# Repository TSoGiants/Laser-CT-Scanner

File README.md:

# About The Shoulders of Giants
In 1676, Isaac Newton, one of the most influential mathematicians and scientists of all time, famously wrote:

> "If I have seen further, it is by standing on the shoulders of giants."

The Shoulders of Giants, Inc. (TSoG) is a nonprofit (501(c)(3)) organization founded in 2013 on a vision that world-class science education should be available to all students of all ages. Since 2015, The Shoulders of Giants has offered an immersive, ongoing mentorship program for dedicated students who would like the opportunity to study more closely under the guidance of Dr. Steven J. Foland. This program is designed to provide middle and high school students with a broad foundation of knowledge and skills across science and engineering disciplines, experience working and communicating in a professional environment, and helps them develop the study habits necessary to achieve success at the university level and beyond.

In 2019, this world-class program became available to students everywhere with the launch of TSoG.tv. This online platform, created in collaboration between The Shoulders of Giants, Inc. and its sister-company Floating Point Laboratories, LLC, provides at-home exercises, live-streaming, and project support to students anywhere in the world.

## About Work in Progress
Work in Progress (WiP) is the main Kepler-level (high school) series on TSoG.tv, focused on multi-disciplinary engineering and applied science.

As the late, great astrophysicist and science advocate Carl Sagan once said: "If you wish to make an apple pie from scratch, you must first invent the universe." With that great quote in mind, this is a series where we bake the whole pie. In each season of Work in Progress we propose a practical project, lay out specifications, then discuss all of the relevant background knowledge necessary to take that project to completion.

Episodes of WiP air live on www.twitch.tv/tsogtv and are archived at www.youtube.com/tsogtv. This project is based on the work completed in episodes that aired on Monday evenings in Summer 2019.

# Laser CT Scanner
## History and Motivation

## Current State
As the name of the series implies, this redesign is currently a work in progress. This section of the README will be kept up-to-date with the current state of the project as the season progresses.

### Design Inputs
* Should function as closely in general operation to an actual CT scanner as possible.
* At least 1 motorized D.O.F.
* Must be able to independently capture a full 2D slice of an opaque object.
* Must be able to transmit raw data to a computer.
* Must be able to adjust height / z-axis of scan on object (manually or otherwise).

### Stretch Goals
* Able to image semi-opaque materials.
* Scanner rotates around subject rather than rotating the subject.
* Motorized z-axis.

### How to Collaborate
For any active TSoG.tv students who would like to contribute to this project, please create a GitHub account and contact Dr. Foland via Discord. He will need your GitHub username to grant you permission to modify this repository.

This project includes mechanical CAD that we will be completing in Alibre Design. You can download a 30 day trial of this software [here](https://www.alibre.com/get-a-trial-of-alibre-design-expert/). Students active on this project should discuss longer-term licensing options with Dr. Foland.

This project also includes electricad CAD that we will be completing in KiCAD. You can download this open source software [here](http://www.kicad.org/).

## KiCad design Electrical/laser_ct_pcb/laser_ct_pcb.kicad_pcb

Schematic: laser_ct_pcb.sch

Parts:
A1: Arduino_Nano_v3.x; Arduino_Nano
C1: 0.1uF; CP_Radial_D5.0mm_P2.50mm
C2: 10uF; CP_Radial_D5.0mm_P2.50mm
J1: Barrel_Jack_Switch; BarrelJack_Horizontal
M1: 28BYJ-48; JST_XH_B5B-XH-AM_1x05_P2.50mm_Vertical
U1, U2: MCP3008; DIP-16_W7.62mm
U3: MIC29310-5.0WT; TO-220-3_Horizontal_TabDown
U4: ULN2003A; DIP-16_W7.62mm

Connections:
+5V: A1.30 (VIN), C2.1, M1.5, U1.15 (Vref), U1.16 (Vdd), U2.15 (Vref), U2.16 (Vdd), U3.3, U4.9; also elsewhere on the board
+VDC: C1.1, J1.1, U3.1
/A: M1.1, U4.16; also elsewhere on the board
/B: M1.2, U4.15; also elsewhere on the board
/C: M1.3, U4.14; also elsewhere on the board
/D: M1.4, U4.13; also elsewhere on the board
/M1: A1.11 (D8), U4.1
/M2: A1.10 (D7), U4.2
/M3: A1.9 (D6), U4.3
/M4: A1.8 (D5), U4.4
/PT2: U1.7 (CH6); also elsewhere on the board
/PT3: U1.6 (CH5); also elsewhere on the board
/PT4: U1.5 (CH4); also elsewhere on the board
/PT5: U1.4 (CH3); also elsewhere on the board
/PT6: U1.3 (CH2); also elsewhere on the board
/PT7: U1.2 (CH1); also elsewhere on the board
/PT8: U1.1 (CH0); also elsewhere on the board
/PT10: U2.7 (CH6); also elsewhere on the board
/PT11: U2.6 (CH5); also elsewhere on the board
/PT12: U2.5 (CH4); also elsewhere on the board
/PT13: U2.4 (CH3); also elsewhere on the board
/PT14: U2.3 (CH2); also elsewhere on the board
/PT15: U2.2 (CH1); also elsewhere on the board
/PT16: U2.1 (CH0); also elsewhere on the board
/Phototransistors/PT1: U1.8 (CH7); also elsewhere on the board
/Phototransistors/PT9: U2.8 (CH7); also elsewhere on the board
/Phototransistors/PT17: A1.26 (A7); also elsewhere on the board
/Phototransistors/PT18: A1.25 (A6); also elsewhere on the board
/Phototransistors/PT19: A1.24 (A5); also elsewhere on the board
/Phototransistors/PT20: A1.23 (A4); also elsewhere on the board
/Phototransistors/PT21: A1.22 (A3); also elsewhere on the board
/Phototransistors/PT22: A1.21 (A2); also elsewhere on the board
/Phototransistors/PT23: A1.20 (A1); also elsewhere on the board
/Phototransistors/PT24: A1.19 (A0); also elsewhere on the board
GND: A1.4 (GND), A1.29 (GND), C1.2, C2.2, J1.2, J1.3, U1.9 (DGND), U1.14 (AGND), U2.9 (DGND), U2.14 (AGND), U3.2, U4.8; also elsewhere on the board
unnamed: A1.12 (D9), U2.10 (~CS~/SHDN)
unnamed: A1.13 (D10), U1.10 (~CS~/SHDN)
unnamed: A1.14 (D11), U1.11 (Din), U2.11 (Din)
unnamed: A1.15 (D12), U1.12 (Dout), U2.12 (Dout)
unnamed: A1.16 (D13), U1.13 (CLK), U2.13 (CLK)

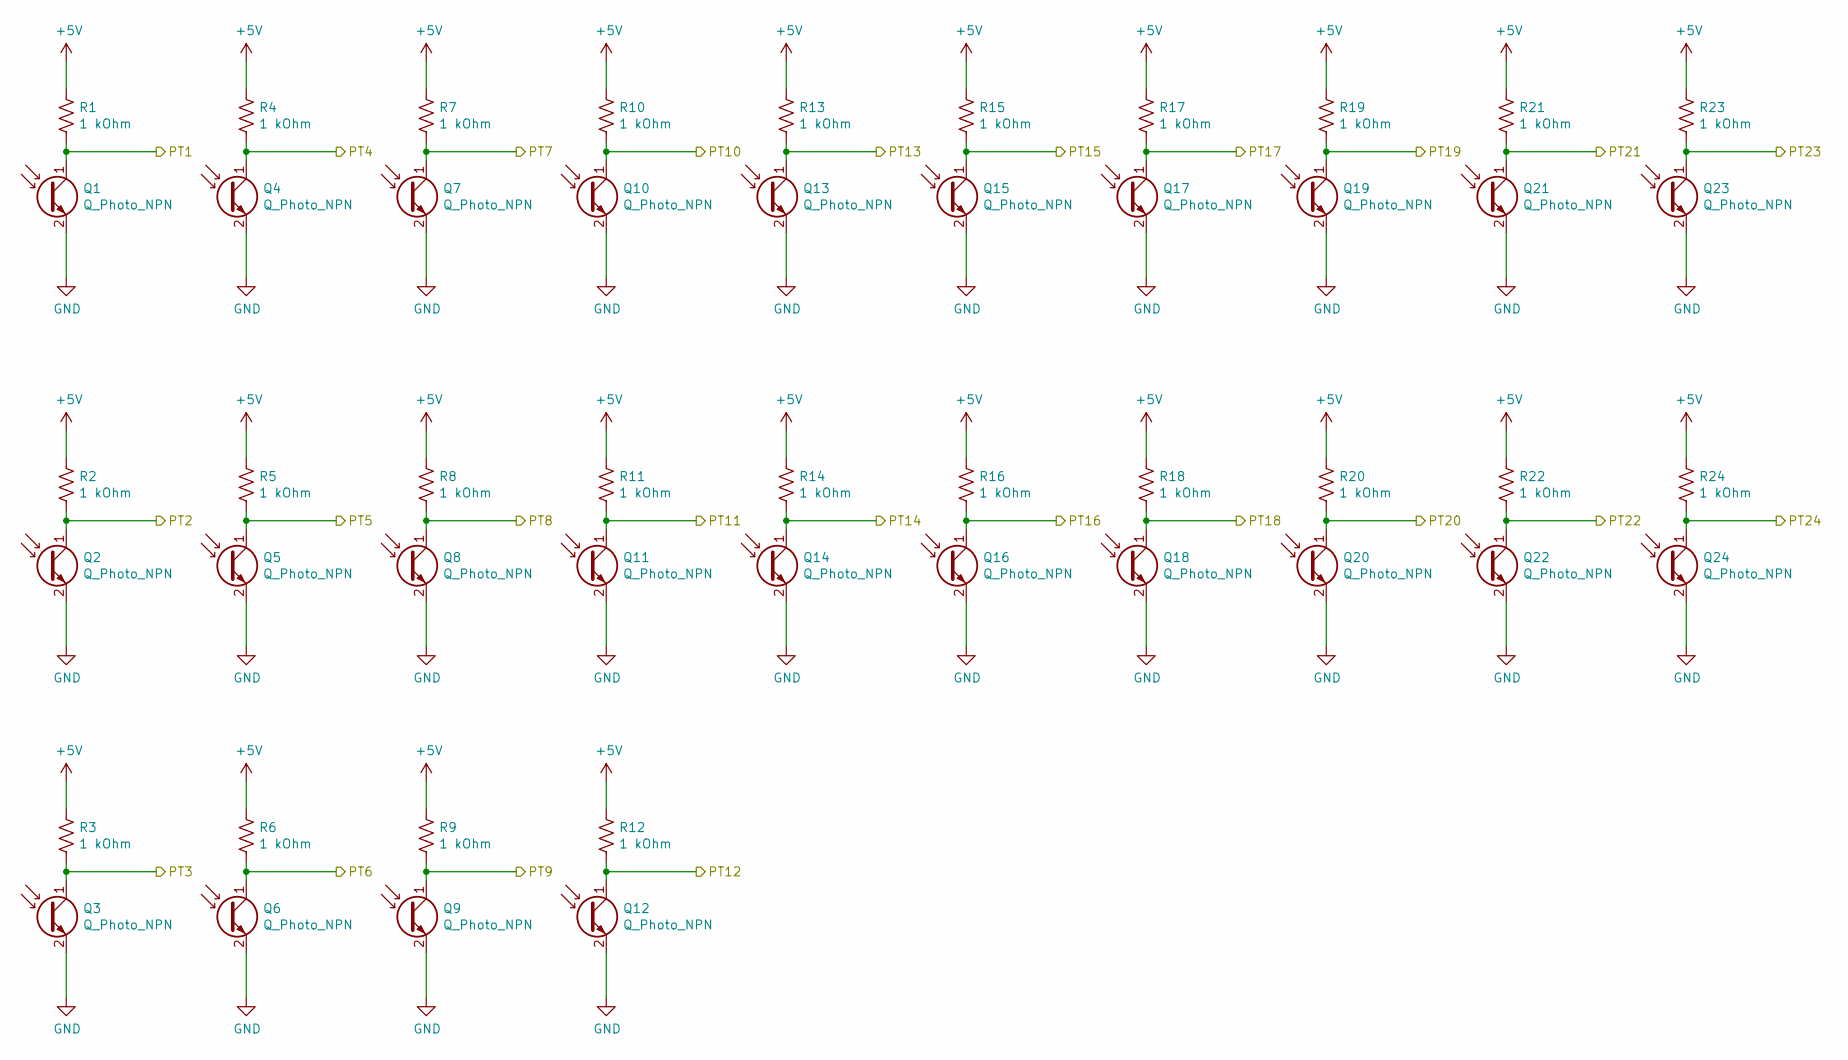
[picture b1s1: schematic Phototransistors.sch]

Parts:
Q1, Q2, Q3, Q4, Q5, Q6, Q7, Q8, Q9, Q10, Q11, Q12, Q13, Q14, Q15, Q16, Q17, Q18, Q19, Q20, Q21, Q22, Q23, Q24: Q_Photo_NPN; LTR_301
R1, R2, R3, R4, R5, R6, R7, R8, R9, R10, R11, R12, R13, R14, R15, R16, R17, R18, R19, R20, R21, R22, R23, R24: 1 kOhm; R_Axial_DIN0204_L3.6mm_D1.6mm_P7.62mm_Horizontal

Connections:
+5V: R1.1, R2.1, R3.1, R4.1, R5.1, R6.1, R7.1, R8.1, R9.1, R10.1, R11.1, R12.1, R13.1, R14.1, R15.1, R16.1, R17.1, R18.1, R19.1, R20.1, R21.1, R22.1, R23.1, R24.1; also elsewhere on the board
/PT2: Q2.1 (C), R2.2; also elsewhere on the board
/PT3: Q3.1 (C), R3.2; also elsewhere on the board
/PT4: Q4.1 (C), R4.2; also elsewhere on the board
/PT5: Q5.1 (C), R5.2; also elsewhere on the board
/PT6: Q6.1 (C), R6.2; also elsewhere on the board
/PT7: Q7.1 (C), R7.2; also elsewhere on the board
/PT8: Q8.1 (C), R8.2; also elsewhere on the board
/PT10: Q10.1 (C), R10.2; also elsewhere on the board
/PT11: Q11.1 (C), R11.2; also elsewhere on the board
/PT12: Q12.1 (C), R12.2; also elsewhere on the board
/PT13: Q13.1 (C), R13.2; also elsewhere on the board
/PT14: Q14.1 (C), R14.2; also elsewhere on the board
/PT15: Q15.1 (C), R15.2; also elsewhere on the board
/PT16: Q16.1 (C), R16.2; also elsewhere on the board
/Phototransistors/PT1: Q1.1 (C), R1.2; also elsewhere on the board
/Phototransistors/PT9: Q9.1 (C), R9.2; also elsewhere on the board
/Phototransistors/PT17: Q17.1 (C), R17.2; also elsewhere on the board
/Phototransistors/PT18: Q18.1 (C), R18.2; also elsewhere on the board
/Phototransistors/PT19: Q19.1 (C), R19.2; also elsewhere on the board
/Phototransistors/PT20: Q20.1 (C), R20.2; also elsewhere on the board
/Phototransistors/PT21: Q21.1 (C), R21.2; also elsewhere on the board
/Phototransistors/PT22: Q22.1 (C), R22.2; also elsewhere on the board
/Phototransistors/PT23: Q23.1 (C), R23.2; also elsewhere on the board
/Phototransistors/PT24: Q24.1 (C), R24.2; also elsewhere on the board
GND: Q1.2 (E), Q2.2 (E), Q3.2 (E), Q4.2 (E), Q5.2 (E), Q6.2 (E), Q7.2 (E), Q8.2 (E), Q9.2 (E), Q10.2 (E), Q11.2 (E), Q12.2 (E), Q13.2 (E), Q14.2 (E), Q15.2 (E), Q16.2 (E), Q17.2 (E), Q18.2 (E), Q19.2 (E), Q20.2 (E), Q21.2 (E), Q22.2 (E), Q23.2 (E), Q24.2 (E); also elsewhere on the board

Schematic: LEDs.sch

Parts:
D1, D2, D3, D4: LED; LED_D5.0mm
H1, H2: MountingHole_Pad; MountingHole_3.5mm
R25, R26, R27, R28: R_US; R_Axial_DIN0204_L3.6mm_D1.6mm_P7.62mm_Horizontal

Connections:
+5V: R25.1, R26.1, R27.1, R28.1; also elsewhere on the board
/A: D1.1; also elsewhere on the board
/B: D2.1; also elsewhere on the board
/C: D3.1; also elsewhere on the board
/D: D4.1; also elsewhere on the board
GND: H1.1, H2.1; also elsewhere on the board
unnamed: D1.2, R25.2
unnamed: D2.2, R26.2
unnamed: D3.2, R27.2
unnamed: D4.2, R28.2

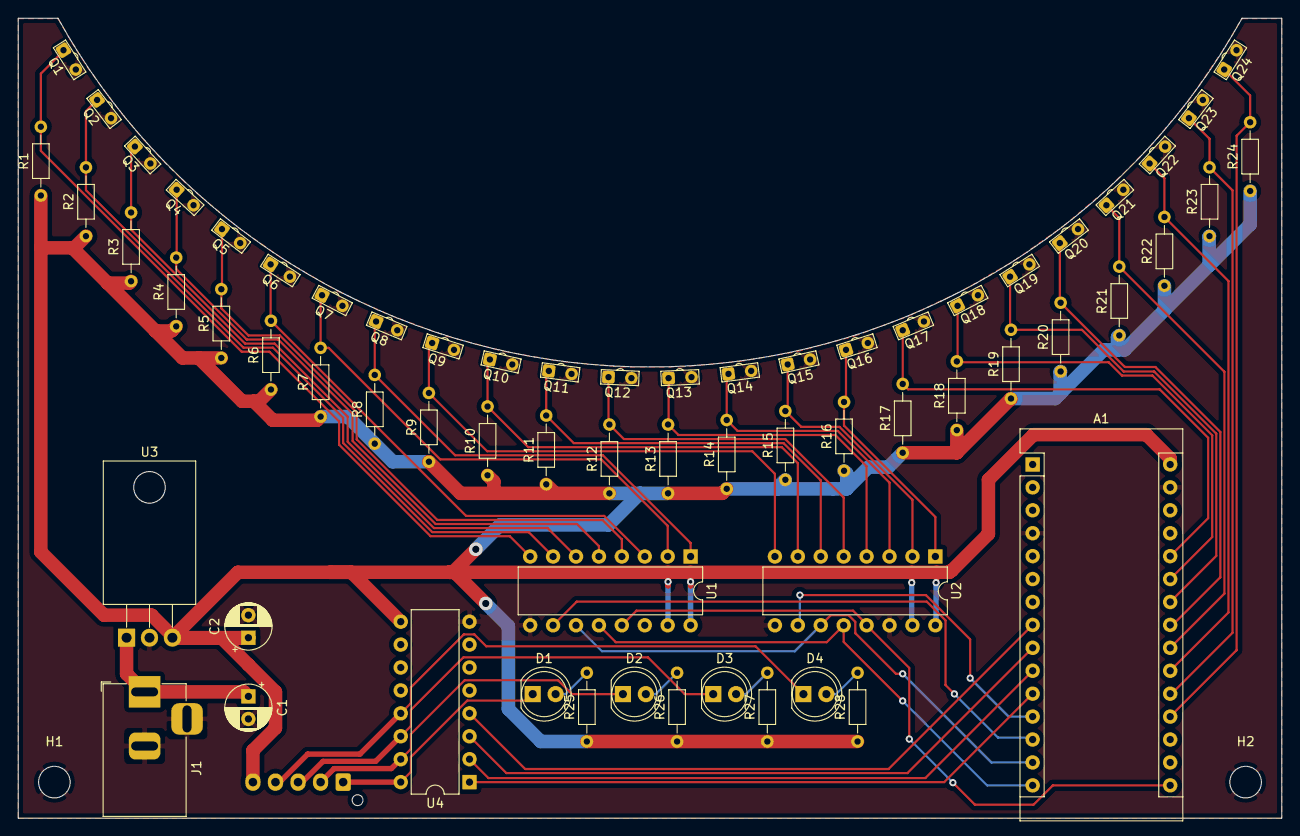
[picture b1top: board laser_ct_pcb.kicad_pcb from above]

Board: 2 copper layers, 140.0 x 88.6 mm, 67 parts (1 on the bottom side), 44 nets.

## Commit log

2019-06-20 Fixed gitignore
2019-06-20 Added license and Readme.
2019-07-10 End of Episode 04.
2019-07-18 End of Episode 05
2019-08-08 End of episode 06.
2019-08-15 End of E07.
2019-08-22 End of Episode 08.
2019-08-22 Fixed through hole size on ICSP board.
2019-08-29 End of episode 09.
2019-09-05 End of episode 10.
2019-09-07 Added LED indicators for motor coils.
2019-09-12 End of episode 11.
2021-11-08 Update README.md
    https://forum.kicad.info/t/warning-avoid-all-links-to-kicad-pcb-org-use-kicad-org/31521
